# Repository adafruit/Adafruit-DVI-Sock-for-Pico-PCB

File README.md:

## Adafruit DVI Sock for Pico - Works with HDMI Displays PCB

<a href="http://www.adafruit.com/products/5957"><br/>
Click here to purchase one from the Adafruit shop</a>

PCB files for the Adafruit DVI Sock for Pico - Works with HDMI Displays. 

Format is EagleCAD schematic and board layout
* https://www.adafruit.com/product/5957

### Description

Wouldn't it be cool to display images and graphics directly from your Pico or Pico W to an HDMI monitor or television? We think so! So we designed this DVI Sock with a digital video output (a.k.a DVI) that will work with any HDMI monitor or display. Note it doesn't do audio, just graphics!

We designed this little breakout board after seeing Wren6991's Pico DVI Sock and their cool demos of the Raspberry Pi Pico driving an HDMI display. By using some fun 'abuse' of overclocking and the RP2040's PIO system, a low-cost microcontroller can have great-looking video output. It's great for making demos or just noodling around with digital video generation.

This breakout board has no active components on it. It's just a connector you can plug an HDMI/DVI cable into, and 220 ohm series resistors. Wire it up to the bottom pins of your Pico board, or solder it directly onto the 'end' like a lil PCB sock. The connections that are made:

* GP12 to D0+
* GP13 to D0-
* GP14 to CK+
* GP15 to CK-
* GP16 to D2+
* GP17 to D2-
* GP18 to D1+
* GP19 to D1-
* Pico GND to GND

We also breakout the 5V, GND, Hot-Plug Detect, CEC and Util pins, for more advanced hacking. Note that while technically you're supposed to provide 5V to the DVI port, it isnt convenient to do so on the Sock so it's left disconnected. Since the 5V is used for the I2C EDID EEPROM and we don't care about it, the 'Sock will work just fine without.

If you want a more fully-featured DVI interface for your Pico, check out the DVI PiCowbell or the all-in-one Adafruit RP2040 DVI Feather.

### License

Adafruit invests time and resources providing this open source design, please support Adafruit and open-source hardware by purchasing products from [Adafruit](https://www.adafruit.com)!

Designed by Limor Fried/Ladyada for Adafruit Industries.

Creative Commons Attribution/Share-Alike, all text above must be included in any redistribution. 
See license.txt for additional details.

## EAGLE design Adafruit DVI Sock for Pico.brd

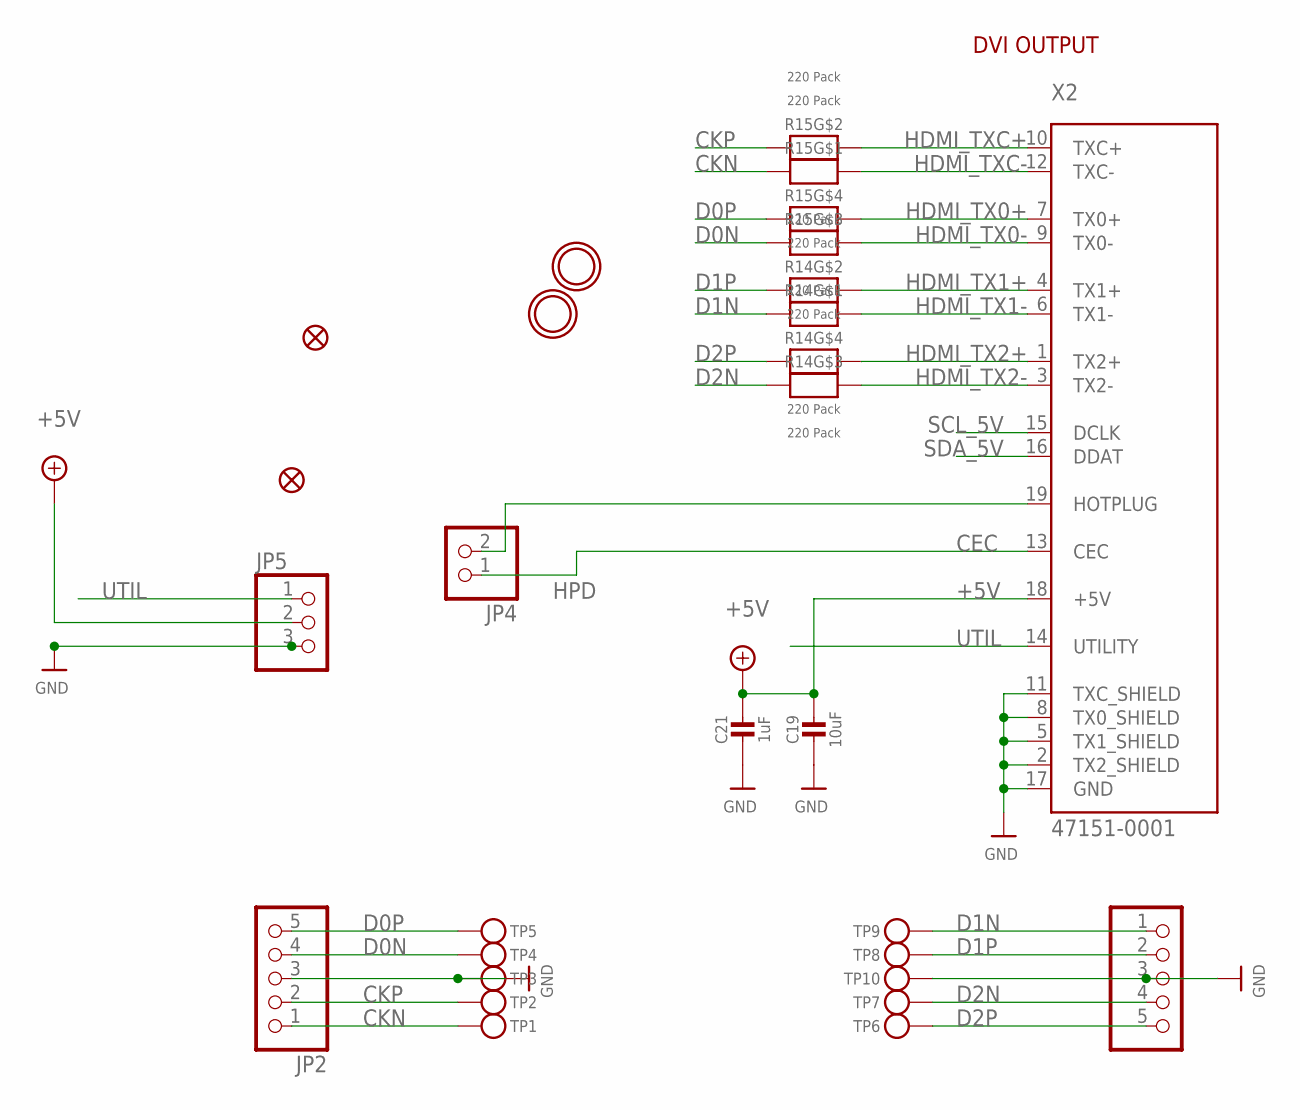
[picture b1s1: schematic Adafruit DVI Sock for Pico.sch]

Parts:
C19: 10uF; 0805-NO
C21: 1uF; 0603-NO
FID1, FID2: FIDUCIAL_1MM
JP2, JP3: HEADER-1X5; 1X05_OVAL
JP4: HEADER-1X2ROUND; 1X02_ROUND
JP5: HEADER-1X3ROUND; 1X03_ROUND
R14, R15: 220 Pack; RESPACK_4X0603
TP1, TP2, TP3, TP4, TP5, TP6, TP7, TP8, TP9, TP10: TESTPOINT_1X3; TESTPOINT_RECT_1X3MM
U$5, U$6: MOUNTINGHOLE2.5; MOUNTINGHOLE_2.5_PLATED
X2: 47151-0001; HDMI_MOLEX_47151-0001

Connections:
+5V: C19.1, C21.1, JP5.2, X2.18 (+5V)
CEC: JP4.1, X2.13 (CEC)
CKN: JP2.1, R15.8 (2), TP1.P$1
CKP: JP2.2, R15.7 (2), TP2.P$1
D0N: JP2.4, R15.6 (2), TP4.P$1
D0P: JP2.5, R15.5 (2), TP5.P$1
D1N: JP3.1, R14.8 (2), TP9.P$1
D1P: JP3.2, R14.7 (2), TP8.P$1
D2N: JP3.4, R14.6 (2), TP7.P$1
D2P: JP3.5, R14.5 (2), TP6.P$1
GND: C19.2, C21.2, JP2.3, JP3.3, JP5.3, TP3.P$1, TP10.P$1, X2.2 (TX2_SHIELD), X2.5 (TX1_SHIELD), X2.8 (TX0_SHIELD), X2.11 (TXC_SHIELD), X2.17 (GND), X2.P$1 (GND), X2.P$2 (GND), X2.P$3 (GND), X2.P$4 (GND)
HDMI_TX0+: R15.4 (1), X2.7 (TX0+)
HDMI_TX0-: R15.3 (1), X2.9 (TX0-)
HDMI_TX1+: R14.2 (1), X2.4 (TX1+)
HDMI_TX1-: R14.1, X2.6 (TX1-)
HDMI_TX2+: R14.4 (1), X2.1 (TX2+)
HDMI_TX2-: R14.3 (1), X2.3 (TX2-)
HDMI_TXC+: R15.2 (1), X2.10 (TXC+)
HDMI_TXC-: R15.1, X2.12 (TXC-)
HPD: JP4.2, X2.19 (HOTPLUG)
SCL_5V: X2.15 (DCLK)
SDA_5V: X2.16 (DDAT)
UTIL: JP5.1, X2.14 (UTILITY)

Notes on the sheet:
DVI OUTPUT

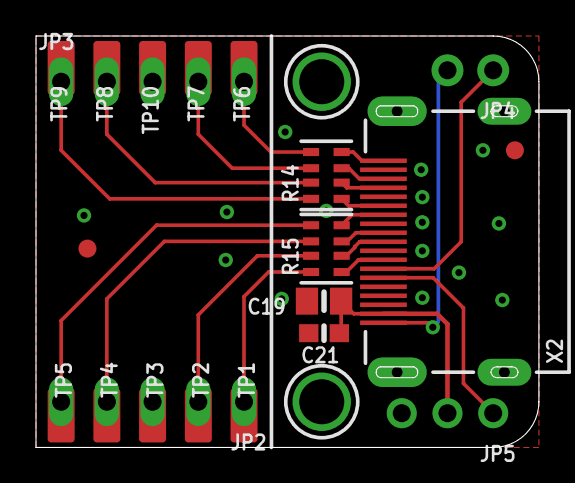
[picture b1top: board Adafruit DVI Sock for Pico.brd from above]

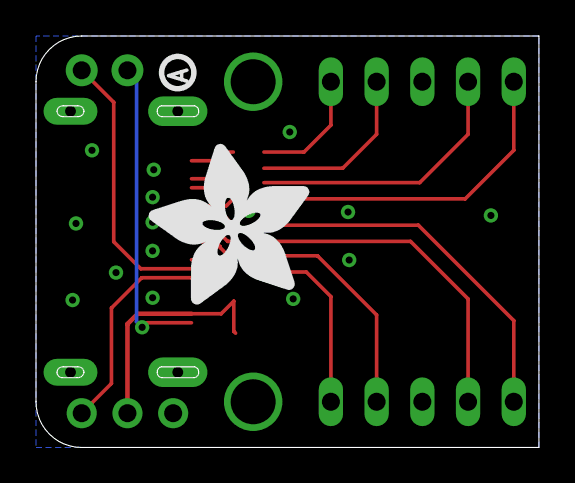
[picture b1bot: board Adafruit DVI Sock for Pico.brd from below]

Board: 2 copper layers, 27.9 x 22.9 mm, 50 parts (13 on the bottom side), 21 nets.

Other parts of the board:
E$1: PCBFEAT-REV-040
PLABEL0: PLABEL0
PLABEL1: PLABEL1
PLABEL2: PLABEL2
PLABEL3: PLABEL3
PLABEL4: PLABEL4
PLABEL5: PLABEL5
PLABEL6: PLABEL6
PLABEL7: PLABEL7
PLABEL9: PLABEL9
PLABEL10: PLABEL10
PLABEL11: PLABEL11
PLABEL12: PLABEL12
PLABEL14: PLABEL14
PLABEL15: PLABEL15
PLABEL16: PLABEL16
PLABEL17: PLABEL17
PLABEL18: PLABEL18
PLABEL19: PLABEL19
PLABEL20: PLABEL20
PLABEL21: PLABEL21
PLABEL22: PLABEL22
PLABEL23: PLABEL23
PLABEL24: PLABEL24
PLABEL25: PLABEL25
PLABEL26: PLABEL26
U$7: ADAFRUIT_9MM

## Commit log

2024-04-30 cookiecutter

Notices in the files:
parts and their libraries:
microbuilder: This work is placed in the public domain, and may be freely used for commercial and non-commercial work with the following conditions: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
